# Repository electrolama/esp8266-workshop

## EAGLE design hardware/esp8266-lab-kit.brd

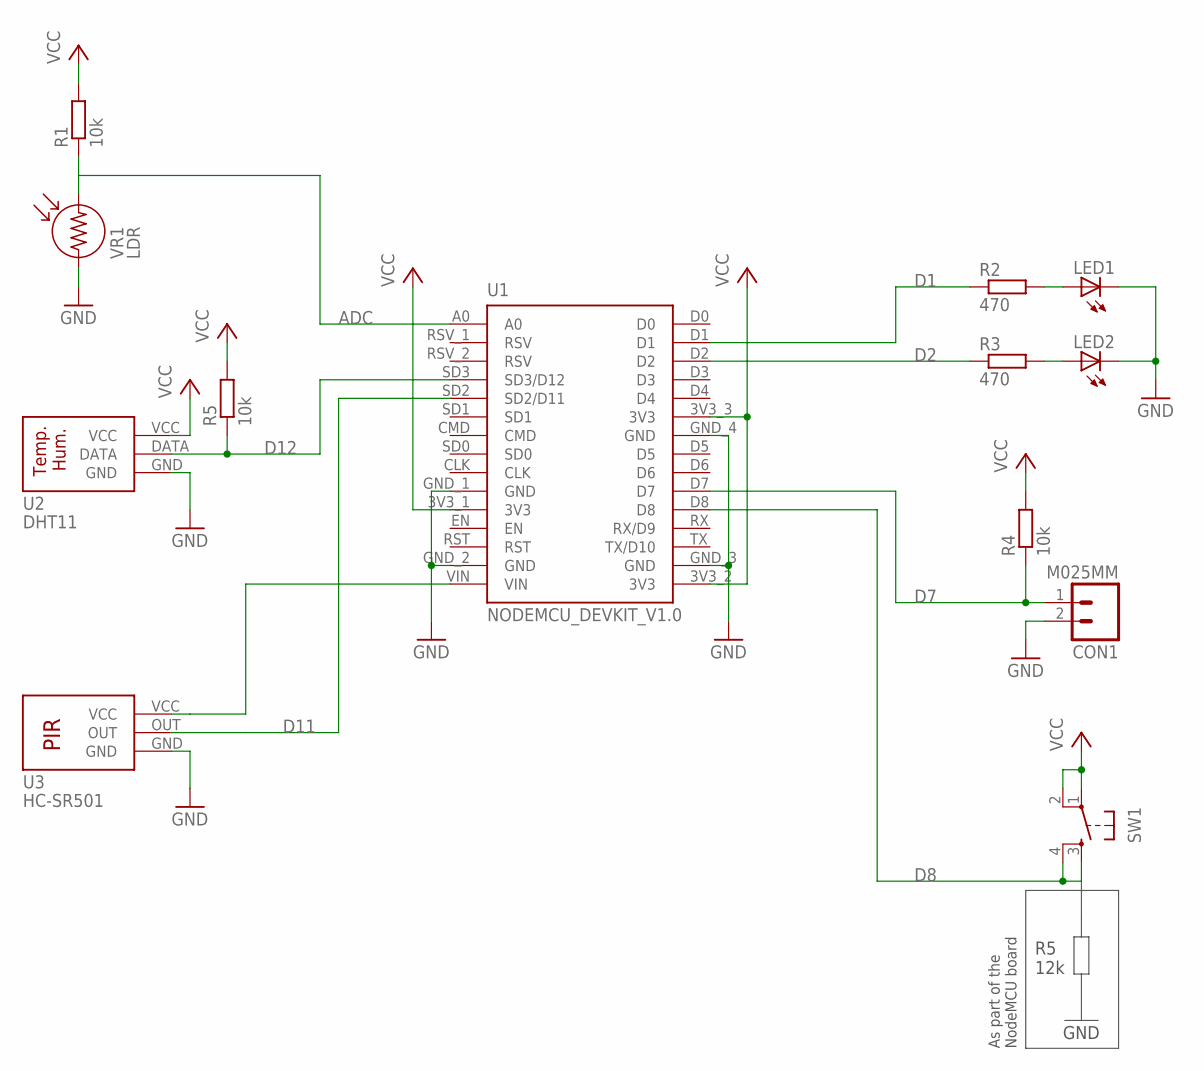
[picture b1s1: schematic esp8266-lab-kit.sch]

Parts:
CON1: M025MM; SCREWTERMINAL-5MM-2
LED1, LED2: LED5MM
R1, R4, R5: 10k; RTH025W
R2, R3: 470; RTH025W
SW1: TAC_SWITCHPTH; TACTILE-PTH
U1: NODEMCU_DEVKIT_V1.0
U2: DHT11
U3: HC-SR501
VR1: LDR

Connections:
ADC: R1.1, U1.A0, VR1.2
D1: R2.1, U1.D1
D2: R3.1, U1.D2
D7: CON1.1, R4.1, U1.D7
D8: SW1.3, SW1.4, U1.D8
D11: U1.SD2 (SD2/D11), U3.OUT
D12: R5.1, U1.SD3 (SD3/D12), U2.DATA
GND: CON1.2, LED1.K (C), LED2.K (C), U1.GND_1 (GND), U1.GND_2 (GND), U1.GND_3 (GND), U1.GND_4 (GND), U2.GND, U3.GND, VR1.1
unnamed: LED1.A, R2.2
unnamed: LED2.A, R3.2
unnamed: U1.VIN, U3.VCC
VCC: R1.2, R4.2, R5.2, SW1.1, SW1.2, U1.3V3_1 (3V3), U1.3V3_2 (3V3), U1.3V3_3 (3V3), U2.VCC

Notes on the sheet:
GND
R5 12k
As part of the NodeMCU board

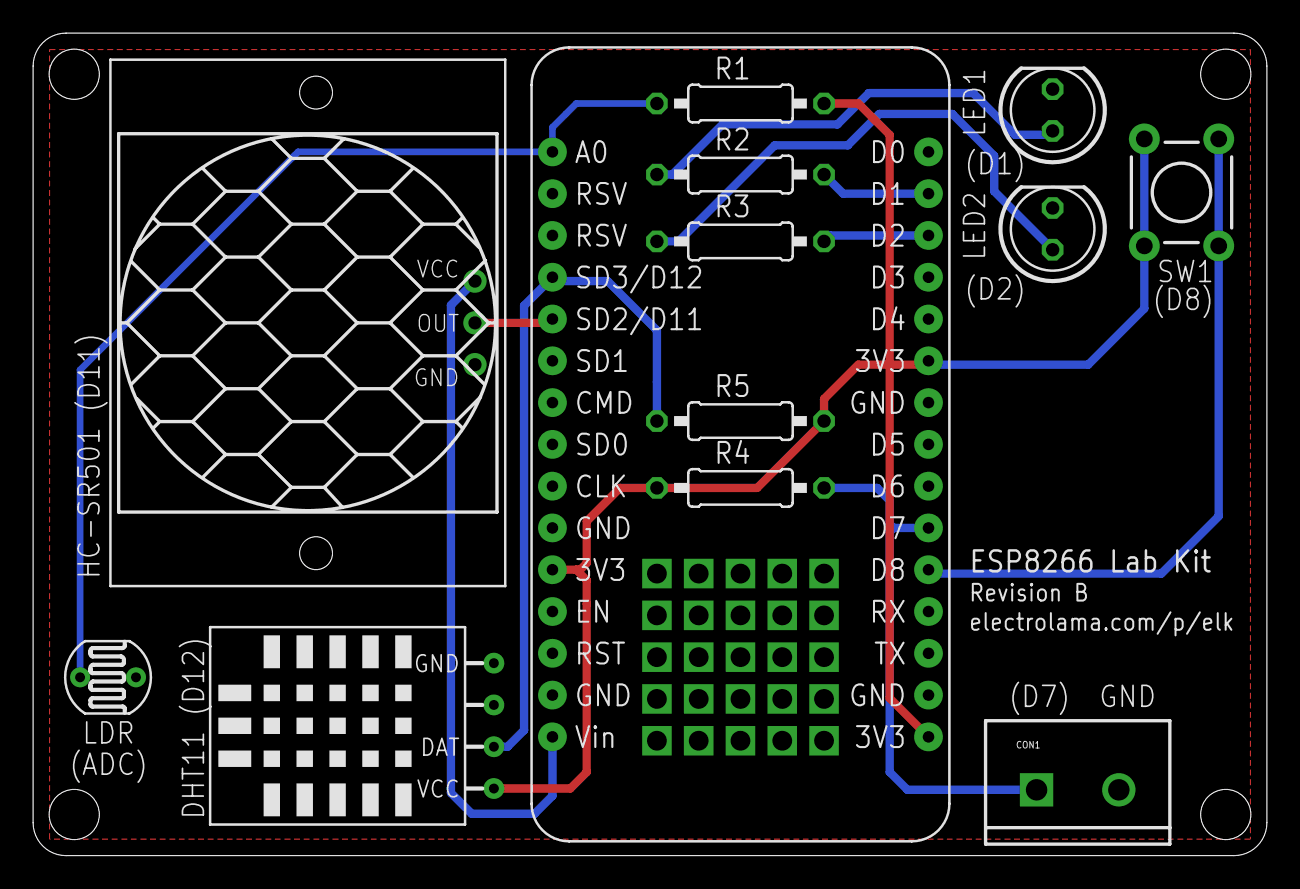
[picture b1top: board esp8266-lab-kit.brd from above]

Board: 2 copper layers, 75.0 x 50.0 mm, 14 parts (0 on the bottom side), 12 nets.

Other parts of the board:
U$1: PROTO_VIAS_05X05-1.2; PROTO_VIAS_05X05_1.2

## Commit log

2015-09-25 add esptool and ESPlorer
2015-09-25 esptool had a .git folder, things are broken :(
2015-09-25 add esptool
2015-09-25 add nodemcu firmware and the helper script
2015-09-25 don't commit the ESPLorer log
2015-09-25 add the esp8266-lab-kit files and datasheets
2015-09-25 initial commit for the code examples
2015-09-25 add PNG version of the schematic
2015-09-27 add updated examples before workshop
2015-09-27 add first version of the lab manual
2015-09-27 add this one too :/
2016-03-19 Update ELK to Revision B, fixing the ADC kerfuffle.

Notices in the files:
parts and their libraries:
SparkFun-Connectors: Licensing: Creative Commons ShareAlike 4.0 International - https://creativecommons.org/licenses/by-sa/4.0
